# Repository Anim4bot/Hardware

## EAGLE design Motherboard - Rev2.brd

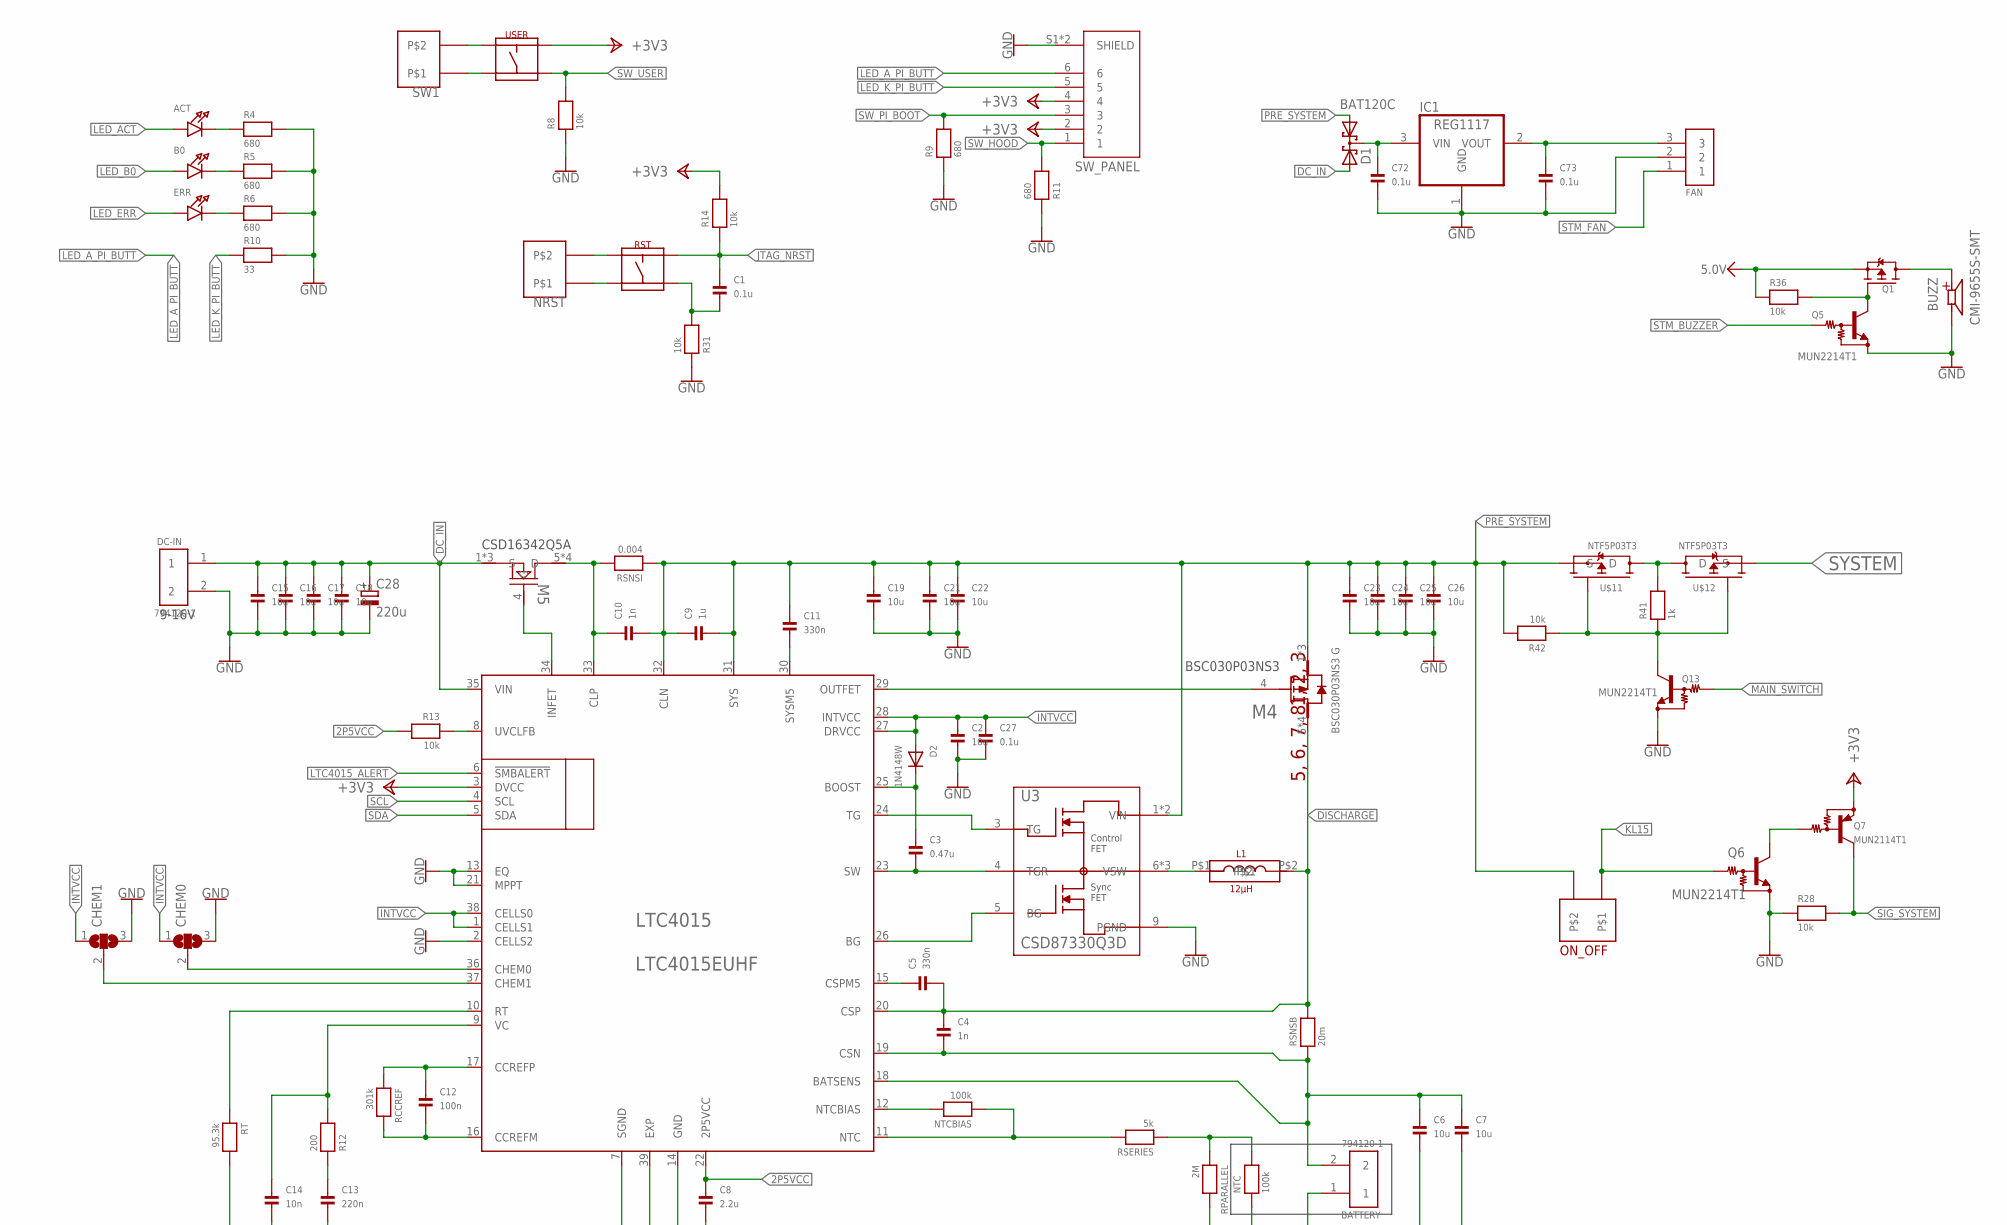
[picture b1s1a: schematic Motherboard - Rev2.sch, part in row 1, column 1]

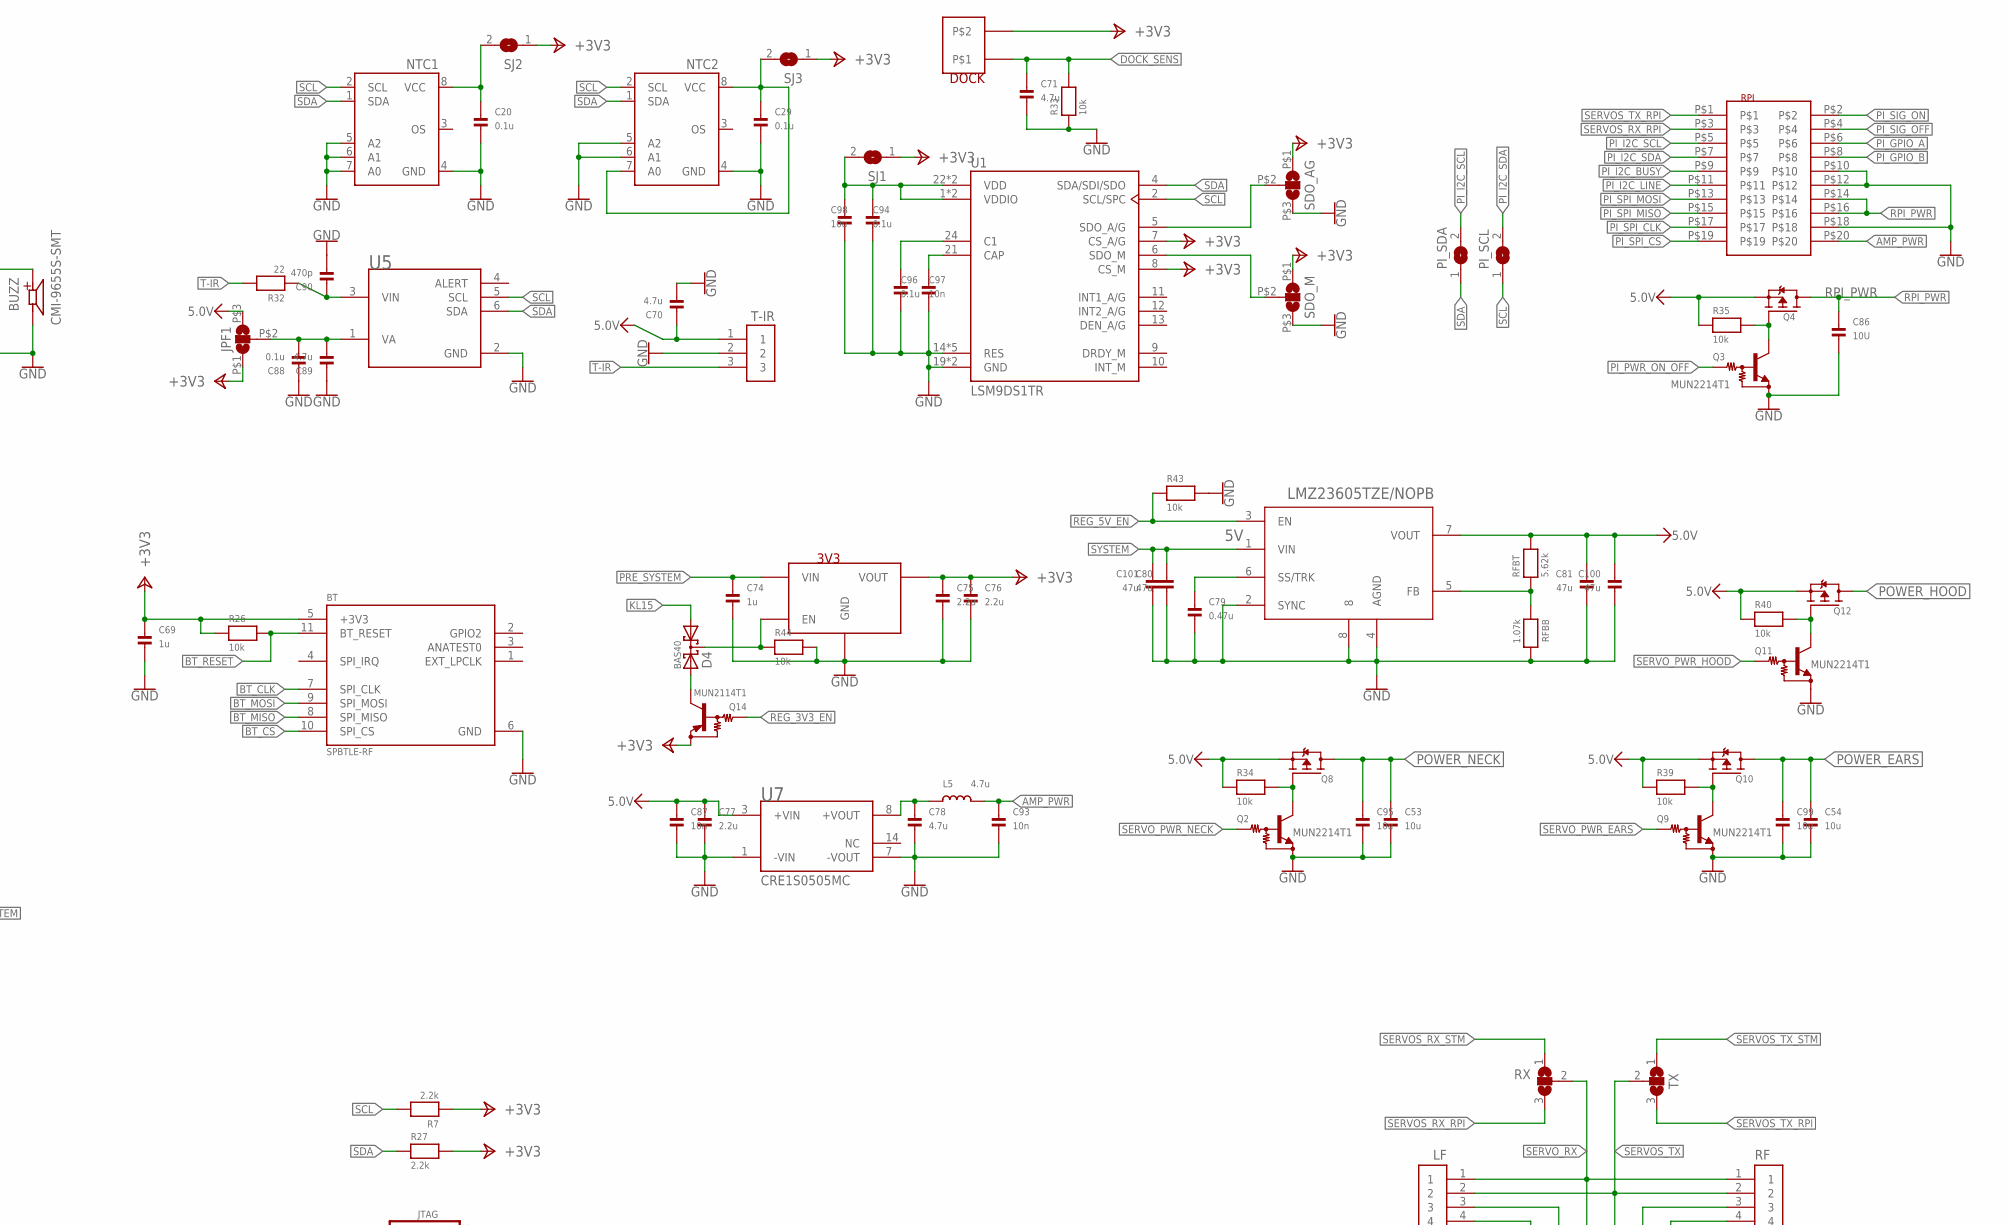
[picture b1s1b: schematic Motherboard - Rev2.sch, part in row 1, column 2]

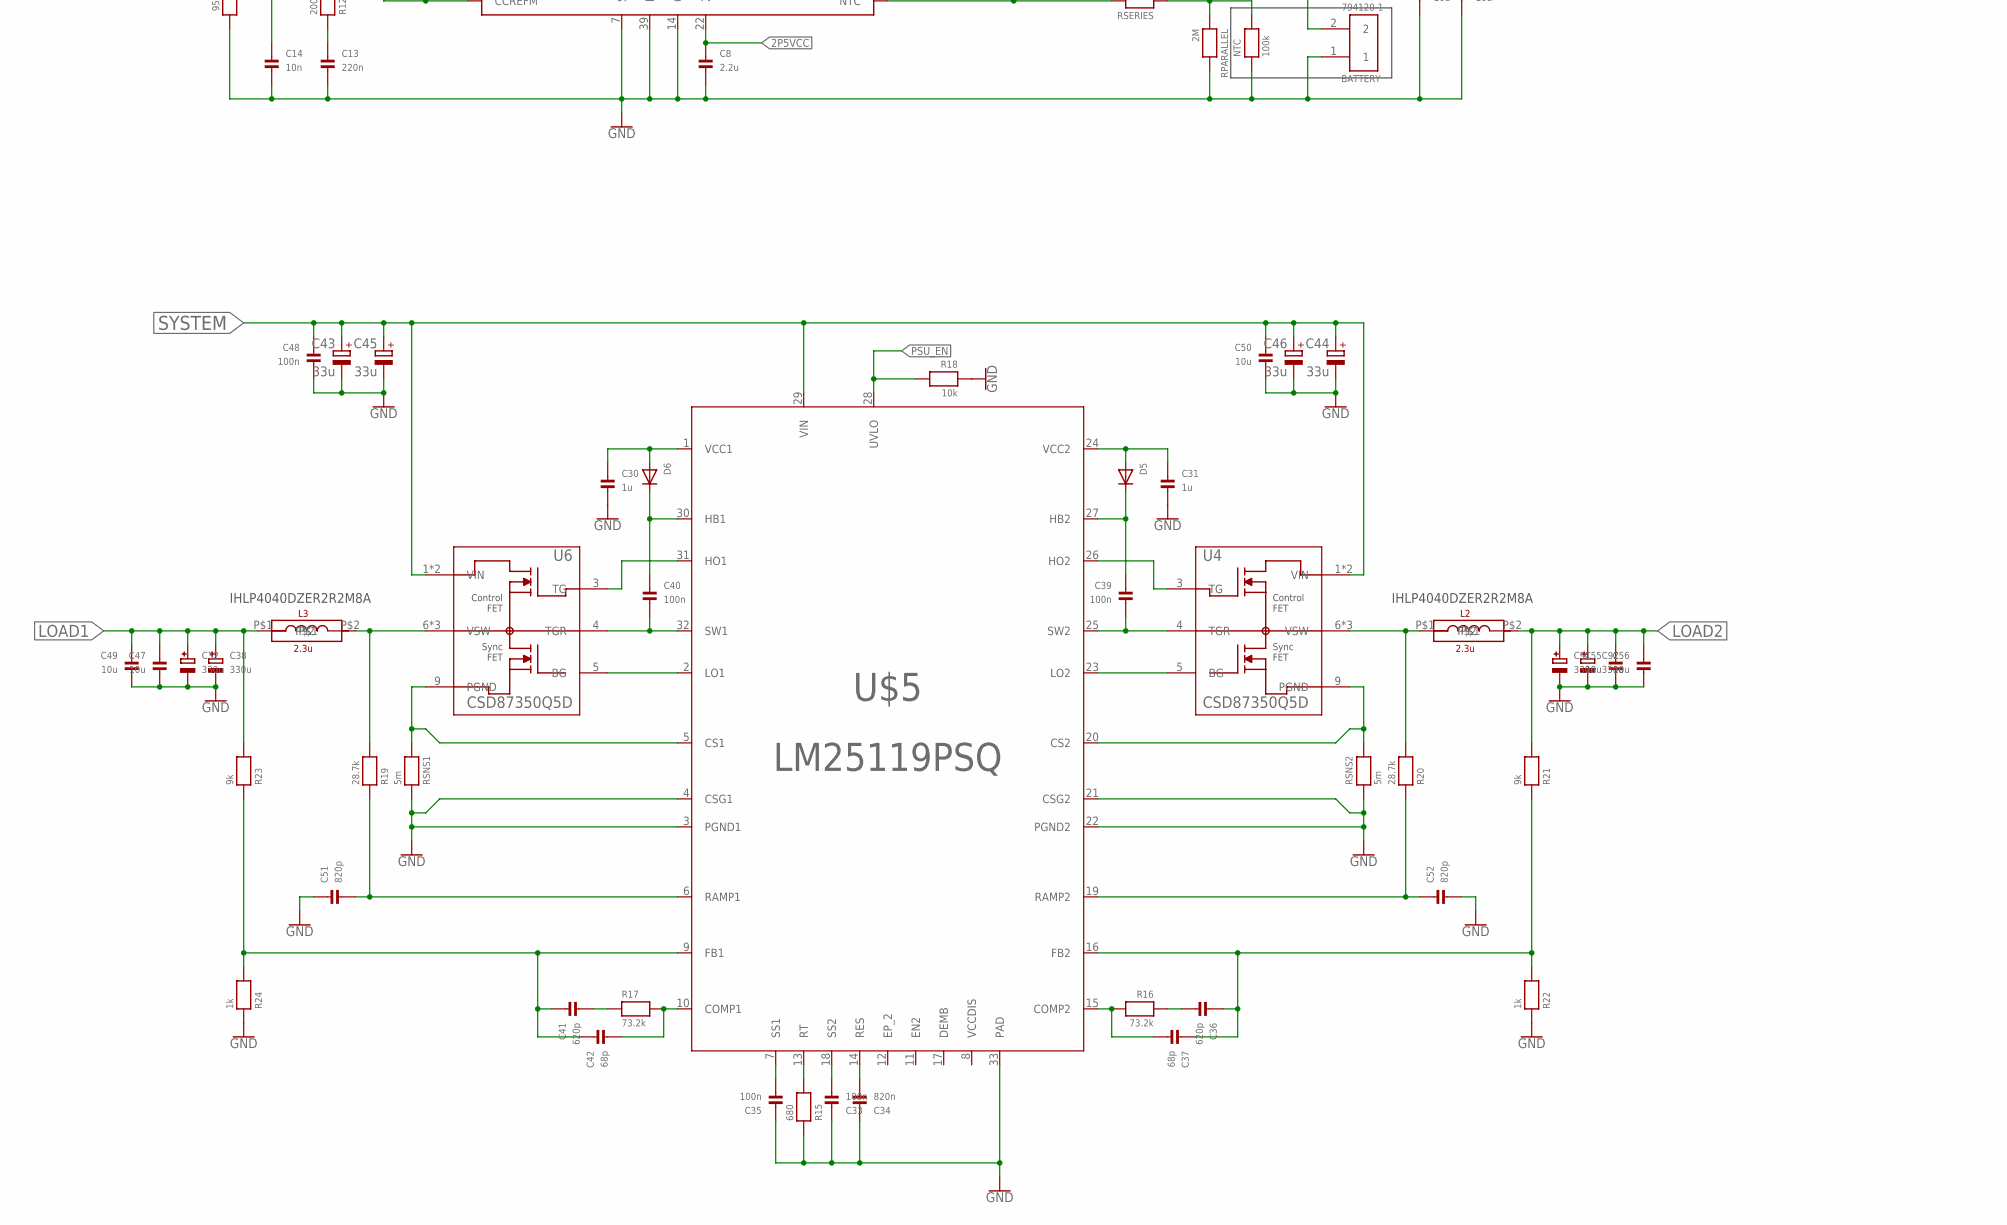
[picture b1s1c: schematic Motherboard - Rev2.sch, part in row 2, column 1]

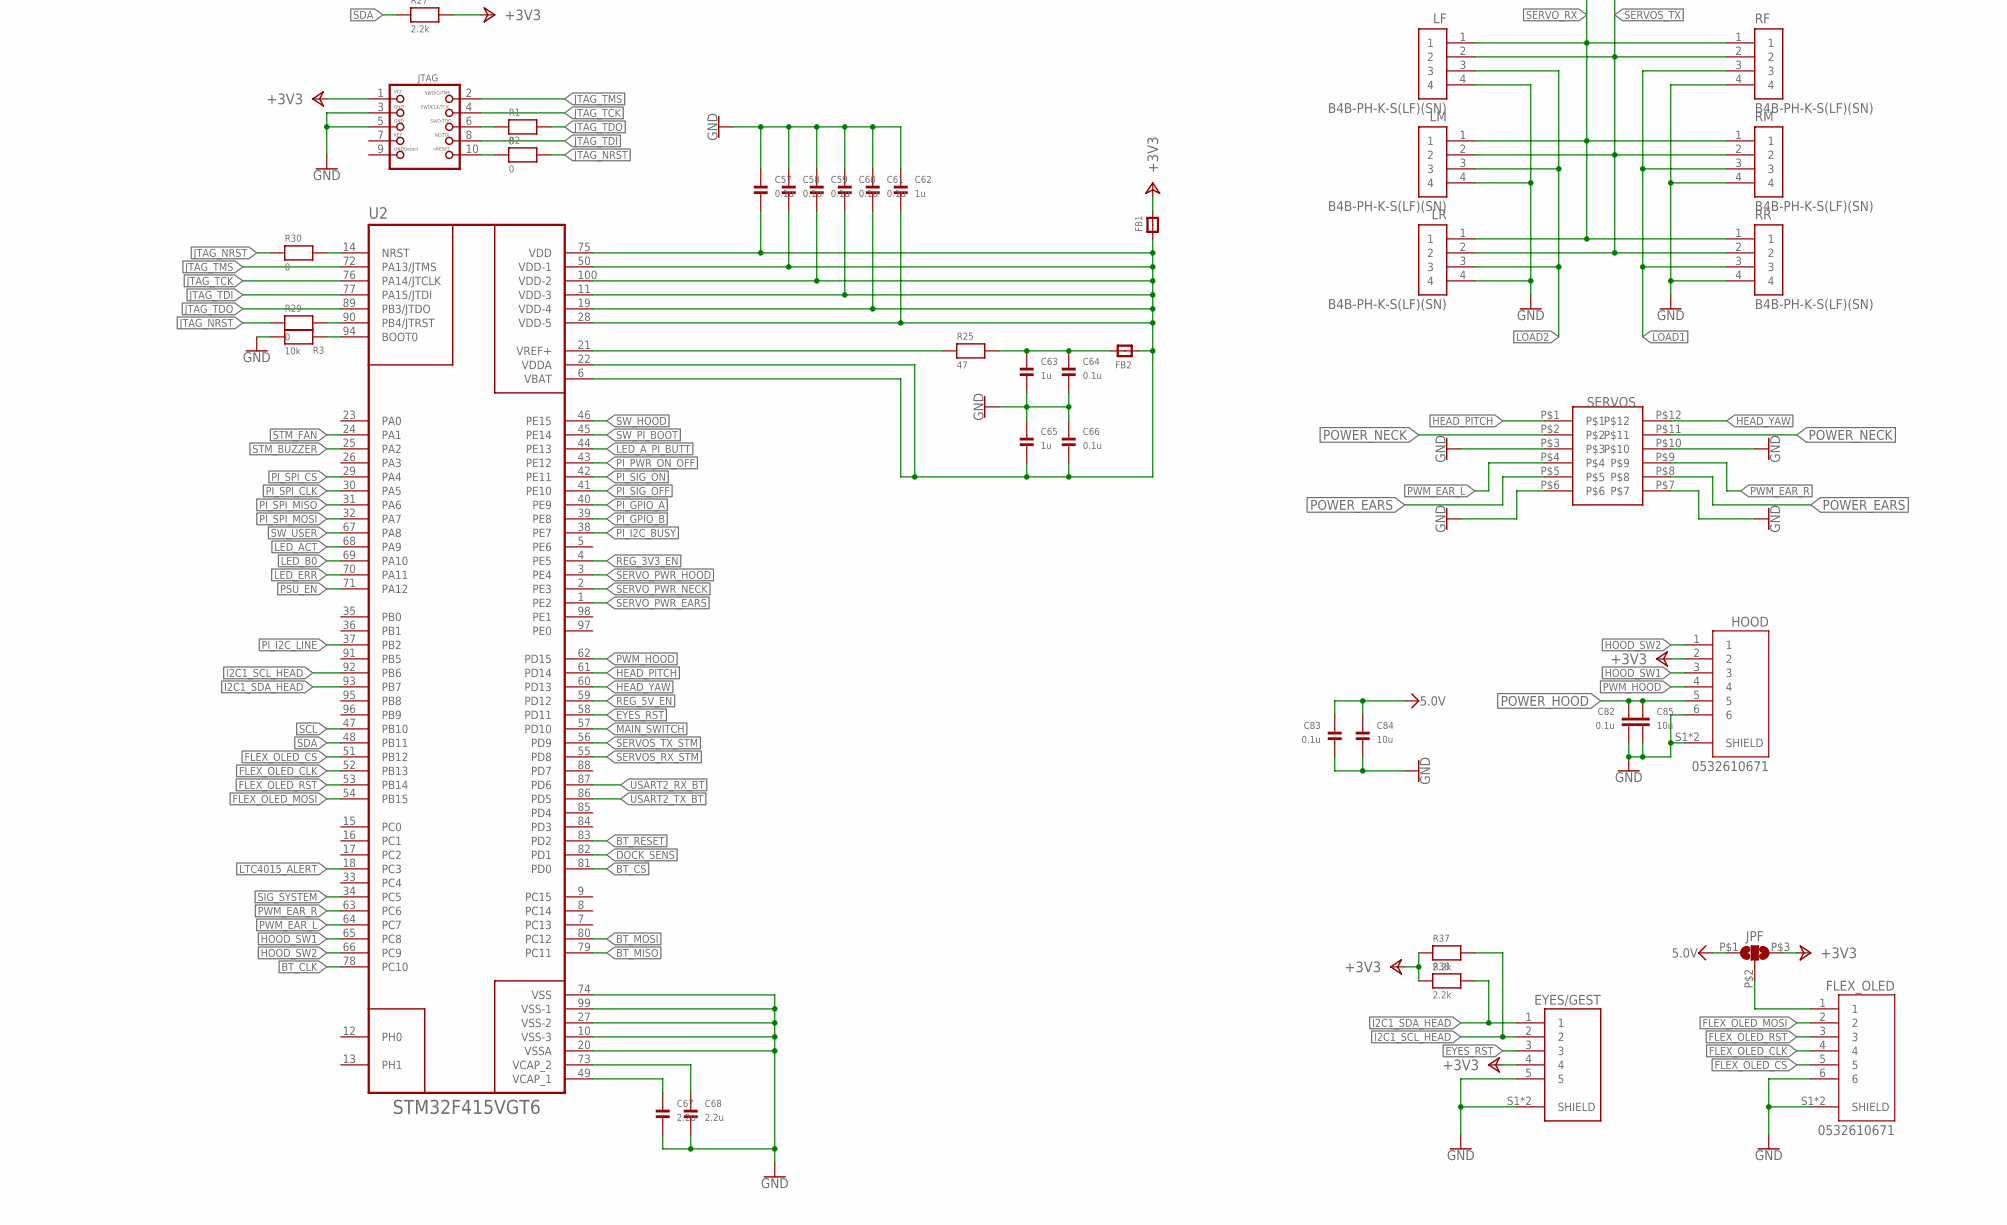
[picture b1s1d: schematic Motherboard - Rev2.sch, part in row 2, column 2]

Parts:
3V3: NCP5500DT-33.50-RKG
5V: LMZ23605TZE/NOPB; TZA07A
ACT: LED0805; CHIPLED_0805
B0: LED0805; CHIPLED_0805
BATTERY: 794120-1; TE_794120-1
BT: SPBTLE-RF; XCVR_SPBTLE-RF
BUZZ: CMI-9655S-SMT; CUI_CMI-9655S-SMT
C1, C20, C27, C29, C57, C58, C59, C60, C61, C64, C66, C72, C73, C82, C83, C88, C94, C96: 0.1u; 0805
C2, C98: 10u; 0805
C3, C79: 0.47u; 0805
C4, C10: 1n; 0805
C5, C11: 330n; 0805
C6, C7, C15, C16, C17, C18, C19, C21, C22, C23, C24, C25, C26, C47, C49, C50, C53, C54, C55, C56, C84, C85, C95, C99: 10u; 1206
C8, C67, C68, C75, C76, C77: 2.2u; 0805
C9, C30, C31, C62, C63, C65, C69, C74: 1u; 0805
C12, C33, C35, C39, C40: 100n; 0805
C13: 220n; 0805
C14, C87, C93, C97: 10n; 0805
C28: 220u; UD-10X10_NICHICON
C32, C38, C91, C92: 330u; EIA7343-31/D-R
C34: 820n; 0805
C36, C41: 620p; 0805
C37, C42: 68p; 0805
C43, C44, C45, C46: 33u; UD-6,3X7,7_NICHICON
C48: 100n; 1206
C51, C52: 820p; 0805
C70, C71, C78, C89: 4.7u; 0805
C80, C81, C100, C101: 47u; 1206
C86: 10U; 0805
C90: 470p; 0805
CHEM0, CHEM1: SJ2W; SJ_2
D1: BAT120C; SOT223
D2: 1N4148W; SOD-123
D4: BAS40; SOT23
D5, D6: DIODESOD-123; SOD-123
DC-IN: 794120-1; TE_794120-1
DOCK: MOLEX_53398
ERR: LED0805; CHIPLED_0805
EYES/GEST: 0532610571; MOLEX_0532610571
FAN: 0532610371; MOLEX_0532610371
FB1, FB2: FERRITE_0805; _0805
FLEX_OLED: 0532610671; MOLEX_0532610671
HOOD: 0532610671; MOLEX_0532610671
IC1: REG1117; SOT223
JPF, JPF1: SJ2WSJ_3; SJ_3
JTAG: JTAG-CORTEXM3; 2X05_1.27MM_SMT
L1: 12µH; SRR1210-680MTR
L2, L3: 2.3u; SRR1210-680MTR
L5: 4.7u; 0805
LF: B4B-PH-K-S(LF)(SN); JST_B4B-PH-K-S(LF)(SN)
LM: B4B-PH-K-S(LF)(SN); JST_B4B-PH-K-S(LF)(SN)
LR: B4B-PH-K-S(LF)(SN); JST_B4B-PH-K-S(LF)(SN)
LTC4015: LTC4015EUHF; QFN50P700X500X80-39N
M4: INFINEON_BSC030P03NS3_GINFINEON_BSC030P03NS3_G_0_0; INFINEON_BSC030P03NS3_G_0
M5: CSD16342Q5A-REV2; DQJ8
NRST: MOLEX_53398
NTC: 100k; 1206
NTC1, NTC2: TEMP_LM75B; TSSOP8
NTCBIAS: 100k; 0805
ON_OFF: MOLEX_53398
PI_SCL: SOLDERJUMPERREFLOW; SOLDERJUMPER_REFLOW
PI_SDA: SOLDERJUMPERREFLOW; SOLDERJUMPER_REFLOW
Q1, Q4, Q8, Q10, Q12: MOSFET-PWIDE; SOT23-WIDE
Q2, Q3, Q5, Q6, Q9, Q11, Q13: MUN2214T1; SC59-BEC
Q7, Q14: MUN2114T1; SC59-BEC
R1, R2, R29, R30: 0; 0805
R3, R8, R13, R14, R18, R26, R28, R31, R33, R34, R35, R36, R39, R40, R42, R43, R44: 10k; 0805
R4, R5, R6, R9, R11, R15: 680; 0805
R7, R27, R37, R38: 2.2k; 0805
R10: 33; 0805
R12: 200; 0805
R16, R17: 73.2k; 0805
R19, R20: 28.7k; 0805
R21, R23: 9k; 0805
R22, R24, R41: 1k; 0805
R25: 47; 0805
R32: 22; 0805
RCCREF: 301k; 0805
RF: B4B-PH-K-S(LF)(SN); JST_B4B-PH-K-S(LF)(SN)
RFBB: 1.07k; 0805
RFBT: 5.62k; 0805
RM: B4B-PH-K-S(LF)(SN); JST_B4B-PH-K-S(LF)(SN)
RPARALLEL: 2M; 0805
RPI: DF50-20DP-1V
RR: B4B-PH-K-S(LF)(SN); JST_B4B-PH-K-S(LF)(SN)
RSERIES: 5k; 0805
RSNS1, RSNS2: 5m; 2012
RSNSB: 20m; 2012
RSNSI: 0.004; 2012
RST: MJTP1140ATR
RT: 95.3k; 0805
RX: SJ2W; SJ_2
SDO_AG: SJ2WSJ_3; SJ_3
SDO_M: SJ2WSJ_3; SJ_3
SERVOS: BM12B-ZPDSS-TF
SJ1, SJ2, SJ3: SOLDERJUMPER; SOLDERJUMPER_ARROW_NOPASTE
SW1: MOLEX_53398
SW_PANEL: 0532610671; MOLEX_0532610671
T-IR: 0532610371; MOLEX_0532610371
TX: SJ2W; SJ_2
U1: LSM9DS1TR; PQFN43P300X350X102-24N
U2: STM32F415VGT6; QFP50P1600X1600X160-100N
U3: CSD87330Q3D; DQZ8_1P8X2P7
U4, U6: CSD87350Q5D; DQY8_3P2X4P3
U5: TEXAS_INSTRUMENTS_ADC101C021CIMK-NOPBTEXAS_INSTRU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; TEXAS_INSTRUMENTS_ADC101C021CIMK-NOPB_0
U7: CRE1S0505MC; SOIC254P1110X700-5N
U$5: LM25119PSQ; SQA32A
U$11, U$12: NTF5P03T3; SOT223
USER: MJTP1140ATR

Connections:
2P5VCC: C8.1, LTC4015.22 (2P5VCC), R13.2
5.0V: 5V.7 (VOUT), C70.1, C77.1, C81.1, C83.1, C84.1, C87.1, C100.1, JPF.P$1 (1), JPF1.P$3 (3), Q1.2 (S), Q4.2 (S), Q8.2 (S), Q10.2 (S), Q12.2 (S), R34.1, R35.1, R36.1, R39.1, R40.1, RFBT.2, T-IR.1, U7.3 (+VIN)
5V_FAN: C73.1, FAN.3, IC1.2 (VOUT)
+3V3: 3V3.VOUT, BT.5 (+3V3), C69.1, C75.1, C76.1, DOCK.P$2, EYES/GEST.4, FB1.2, HOOD.2, JPF.P$3 (3), JPF1.P$1 (1), JTAG.1, LTC4015.3 (DVCC), Q7.E, Q14.E, R7.1, R14.2, R26.1, R27.2, R37.1, R38.1, SDO_AG.P$1 (1), SDO_M.P$1 (1), SJ1.1, SJ2.1, SJ3.1, SW_PANEL.2, SW_PANEL.4, U1.7 (CS_A/G), U1.8 (CS_M), USER.P$2
AMP_PWR: C93.1, L5.2, RPI.P$20
BATT: BATTERY.2, C4.2, C6.1, C7.1, LTC4015.18 (BATSENS), LTC4015.19 (CSN), RSNSB.1
BG: LTC4015.26 (BG), U3.5 (BG)
BT_CLK: BT.7 (SPI_CLK), U2.78 (PC10)
BT_CS: BT.10 (SPI_CS), U2.81 (PD0)
BT_MISO: BT.8 (SPI_MISO), U2.79 (PC11)
BT_MOSI: BT.9 (SPI_MOSI), U2.80 (PC12)
BT_RESET: BT.11 (BT_RESET), R26.2, U2.83 (PD2)
CCREFM: C12.2, LTC4015.16 (CCREFM), RCCREF.2
CCREFP: C12.1, LTC4015.17 (CCREFP), RCCREF.1
CHEM0: CHEM0.2, LTC4015.36 (CHEM0)
CHEM1: CHEM1.2, LTC4015.37 (CHEM1)
CLP: C10.1, LTC4015.33 (CLP), M5.5 (D), M5.6 (D), M5.7 (D), M5.8 (D), RSNSI.2
COMP1: C42.2, R17.2, U$5.10 (COMP1)
COMP2: C37.2, R16.2, U$5.15 (COMP2)
CS1: RSNS1.2, U6.9 (PGND), U$5.5 (CS1)
CS2: RSNS2.2, U4.9 (PGND), U$5.20 (CS2)
DC_IN: C15.1, C16.1, C17.1, C18.1, C28.+, D1.3 (A2), DC-IN.1, LTC4015.35 (VIN), M5.1 (S), M5.2 (S), M5.3 (S)
DISCHARGE: C4.1, C5.2, L1.P$2, LTC4015.20 (CSP), M4.5 (2_DRAIN), M4.6 (2_DRAIN), M4.7 (2_DRAIN), M4.8 (2_DRAIN), RSNSB.2
DOCK_SENS: C71.1, DOCK.P$1, R33.2, U2.82 (PD1)
EYES_RST: EYES/GEST.3, U2.58 (PD11)
FB1: C41.1, C42.1, R23.1, R24.2, U$5.9 (FB1)
FB2: C36.1, C37.1, R21.1, R22.2, U$5.16 (FB2)
FLEX_OLED_CLK: FLEX_OLED.4, U2.52 (PB13)
FLEX_OLED_CS: FLEX_OLED.5, U2.51 (PB12)
FLEX_OLED_MOSI: FLEX_OLED.2, U2.54 (PB15)
FLEX_OLED_RST: FLEX_OLED.3, U2.53 (PB14)
GND: 3V3.GND, 5V.2 (SYNC), 5V.4 (AGND), 5V.8, BATTERY.1, BT.6 (GND), BUZZ.N, C2.2, C6.2, C7.2, C8.2, C13.2, C14.2, C15.2, C16.2, C17.2, C18.2, C19.2, C20.2, C21.2, C22.2, C23.2, C24.2, C25.2, C26.2, C27.2, C28.-, C29.2, C30.2, C31.2, C32.-, C33.1, C34.1, C35.1, C38.-, C43.-, C44.-, C45.-, C46.-, C47.2, C48.2, C49.2, C50.2, C51.1, C52.2, C53.2, C54.2, C55.2, C56.2, C57.1, C58.1, C59.1, C60.1, C61.1, C62.1, C63.2, C64.2, C65.1, C66.1, C67.2, C68.2, C69.2, C70.2, C71.2, C72.2, C73.2, C74.2, C75.2, C76.2, C77.2, C78.2, C79.2, C80.2, C81.2, C82.2, C83.2, C84.2, C85.2, C86.2, C87.2, C88.1, C89.1, C90.2, C91.-, C92.-, C93.2, C94.2, C95.2, C96.2, C97.2, C98.2, C99.2, C100.2, C101.2, CHEM0.3, CHEM1.3, DC-IN.2, EYES/GEST.5, EYES/GEST.S1 (SHIELD), EYES/GEST.S2 (SHIELD), FAN.2, FLEX_OLED.6, FLEX_OLED.S1 (SHIELD), FLEX_OLED.S2 (SHIELD), HOOD.6, HOOD.S1 (SHIELD), HOOD.S2 (SHIELD), IC1.1 (GND), JTAG.3, JTAG.5, LF.4, LM.4, LR.4, LTC4015.2 (CELLS2), LTC4015.7 (SGND), LTC4015.13 (EQ), LTC4015.14 (GND), LTC4015.21 (MPPT), LTC4015.39 (EXP), NTC.1, NTC1.4 (GND), NTC1.5 (A2), NTC1.6 (A1), NTC1.7 (A0), NTC2.4 (GND), NTC2.5 (A2), NTC2.6 (A1), Q2.E, Q3.E, Q5.E, Q6.E, Q9.E, Q11.E, Q13.E, R3.1, R4.2, R5.2, R6.2, R8.1, R9.1, R10.2, R11.1, R15.1, R18.1, R22.1, R24.1, R28.1, R31.1, R33.1, R43.2, R44.2, RF.4, RFBB.2, RM.4, RPARALLEL.2, RPI.P$10, RPI.P$12, RPI.P$18, RR.4, RSNS1.1, RSNS2.1, RT.2, SDO_AG.P$3 (3), SDO_M.P$3 (3), SERVOS.P$3, SERVOS.P$6, SERVOS.P$7, SERVOS.P$10, SW_PANEL.S1 (SHIELD), SW_PANEL.S2 (SHIELD), T-IR.2, U1.14 (RES), U1.15 (RES), U1.16 (RES), U1.17 (RES), U1.18 (RES), U1.19 (GND), U1.20 (GND), U2.10 (VSS-3), U2.20 (VSSA), U2.27 (VSS-2), U2.74 (VSS), U2.99 (VSS-1), U3.9 (PGND), U5.2 (GND), U7.1 (-VIN), U7.7 (-VOUT), U$5.3 (PGND1), U$5.4 (CSG1), U$5.21 (CSG2), U$5.22 (PGND2), U$5.33 (PAD)
HEAD_PITCH: SERVOS.P$1, U2.61 (PD14)
HEAD_YAW: SERVOS.P$12, U2.60 (PD13)
HO1: U6.3 (TG), U$5.31 (HO1)
HO2: U4.3 (TG), U$5.26 (HO2)
HOOD_SW1: HOOD.3, U2.65 (PC8)
HOOD_SW2: HOOD.1, U2.66 (PC9)
I2C1_SCL_HEAD: EYES/GEST.2, R37.2, U2.92 (PB6)
I2C1_SDA_HEAD: EYES/GEST.1, R38.2, U2.93 (PB7)
INFET: LTC4015.34 (INFET), M5.4 (G)
INTVCC: C2.1, C27.1, CHEM0.1, CHEM1.1, D2.A, LTC4015.1 (CELLS1), LTC4015.27 (DRVCC), LTC4015.28 (INTVCC), LTC4015.38 (CELLS0)
JTAG_NRST: C1.1, R2.2, R14.1, R29.1, R30.1, RST.P$2
JTAG_TCK: JTAG.4, U2.76 (PA14/JTCLK)
JTAG_TDI: JTAG.8, U2.77 (PA15/JTDI)
JTAG_TDO: R1.2, U2.89 (PB3/JTDO)
JTAG_TMS: JTAG.2, U2.72 (PA13/JTMS)
KL15: D4.1 (A1), ON_OFF.P$1, Q6.B
LED_ACT: ACT.A, U2.68 (PA9)
LED_A_PI_BUTT: SW_PANEL.6, U2.44 (PE13)
LED_B0: B0.A, U2.69 (PA10)
LED_ERR: ERR.A, U2.70 (PA11)
LED_K_PI_BUTT: R10.1, SW_PANEL.5
LO1: U6.5 (BG), U$5.2 (LO1)
LO2: U4.5 (BG), U$5.23 (LO2)
LOAD1: C32.+, C38.+, C47.1, C49.1, L3.P$1, R23.2, RF.3, RM.3, RR.3
LOAD2: C55.1, C56.1, C91.+, C92.+, L2.P$2, LF.3, LM.3, LR.3, R21.2
LTC4015_ALERT: LTC4015.6 (!SMBALERT), U2.18 (PC3)
MAIN_SWITCH: Q13.B, U2.57 (PD10)
unnamed: C90.1, R32.1, U5.3 (VIN)
unnamed: NRST.P$1, RST.P$4
unnamed: Q2.C, Q8.1 (G), R34.2
unnamed: Q3.C, Q4.1 (G), R35.2
unnamed: ERR.C, R6.1
unnamed: B0.C, R5.1
unnamed: JTAG.6, R1.1
unnamed: JTAG.10, R2.1
unnamed: ACT.C, R4.1
unnamed: C72.1, D1.4 (K1K2), IC1.3 (VIN)
unnamed: NRST.P$2, RST.P$1
unnamed: Q9.C, Q10.1 (G), R39.2
unnamed: C78.1, L5.1, U7.8 (+VOUT)
unnamed: LTC4015.12 (NTCBIAS), NTCBIAS.2
unnamed: Q11.C, Q12.1 (G), R40.2
unnamed: C3.1, D2.C, LTC4015.25 (BOOST)
unnamed: R29.2, U2.90 (PB4/JTRST)
unnamed: R3.2, U2.94 (BOOT0)
unnamed: R41.2, U$11.4 (D), U$12.4 (D)
unnamed: C5.1, LTC4015.15 (CSPM5)
unnamed: Q13.C, R41.1, R42.1, U$11.1 (G), U$12.1 (G)
unnamed: Q1.1 (G), Q5.C, R36.2
unnamed: Q6.C, Q7.B
unnamed: R30.2, U2.14 (NRST)
unnamed: SW1.P$1, USER.P$4
unnamed: 3V3.EN, D4.3 (C), R44.1
unnamed: C13.1, R12.1
unnamed: D4.2 (A2), Q14.C
unnamed: C1.2, R31.2, RST.P$3
unnamed: C68.1, U2.73 (VCAP_2)
unnamed: LTC4015.8 (UVCLFB), R13.1
unnamed: R15.2, U$5.13 (RT)
unnamed: C67.1, U2.49 (VCAP_1)
unnamed: BUZZ.P, Q1.3 (D)
unnamed: R25.1, U2.21 (VREF+)
unnamed: C36.2, R16.1
unnamed: C57.2, C58.2, C59.2, C60.2, C61.2, C62.2, C65.2, C66.2, FB1.1, FB2.1, U2.6 (VBAT), U2.11 (VDD-3), U2.19 (VDD-4), U2.22 (VDDA), U2.28 (VDD-5), U2.50 (VDD-1), U2.75 (VDD), U2.100 (VDD-2)
unnamed: C63.1, C64.1, FB2.2, R25.2
unnamed: C39.1, D5.C, U$5.27 (HB2)
unnamed: NTC.2, RPARALLEL.1, RSERIES.1
unnamed: C96.1, U1.24 (C1)
unnamed: C97.1, U1.21 (CAP)
unnamed: SDO_M.P$2 (2), U1.6 (SDO_M)
unnamed: SDO_AG.P$2 (2), U1.5 (SDO_A/G)
unnamed: FLEX_OLED.1, JPF.P$2 (2)
unnamed: C88.2, C89.2, JPF1.P$2 (2), U5.1 (VA)
unnamed: SW1.P$2, USER.P$1
unnamed: C40.1, D6.C, U$5.30 (HB1)
unnamed: 5V.5 (FB), RFBB.1, RFBT.1
unnamed: C20.1, NTC1.8 (VCC), SJ2.2
unnamed: C41.2, R17.1
unnamed: C94.1, C98.1, SJ1.2, U1.1 (VDDIO), U1.3 (VDDIO), U1.22 (VDD), U1.23 (VDD)
unnamed: 5V.6 (SS/TRK), C79.1
unnamed: C29.1, NTC2.7 (A0), NTC2.8 (VCC), SJ3.2
unnamed: L3.P$2, R19.2, U6.6 (VSW), U6.7 (VSW), U6.8 (VSW)
unnamed: L2.P$1, R20.2, U4.6 (VSW), U4.7 (VSW), U4.8 (VSW)
NTC: LTC4015.11 (NTC), NTCBIAS.1, RSERIES.2
OUTFET: LTC4015.29 (OUTFET), M4.4 (GATE)
PI_GPIO_A: RPI.P$6, U2.40 (PE9)
PI_GPIO_B: RPI.P$8, U2.39 (PE8)
PI_I2C_BUSY: RPI.P$9, U2.38 (PE7)
PI_I2C_LINE: RPI.P$11, U2.37 (PB2)
PI_I2C_SCL: PI_SDA.2, RPI.P$5
PI_I2C_SDA: PI_SCL.2, RPI.P$7
PI_PWR_ON_OFF: Q3.B, U2.43 (PE12)
PI_SIG_OFF: RPI.P$4, U2.41 (PE10)
PI_SIG_ON: RPI.P$2, U2.42 (PE11)
PI_SPI_CLK: RPI.P$17, U2.30 (PA5)
PI_SPI_CS: RPI.P$19, U2.29 (PA4)
PI_SPI_MISO: RPI.P$15, U2.31 (PA6)
PI_SPI_MOSI: RPI.P$13, U2.32 (PA7)
POWER_EARS: C54.1, C99.1, Q10.3 (D), SERVOS.P$5, SERVOS.P$8
POWER_HOOD: C82.1, C85.1, HOOD.5, Q12.3 (D)
POWER_NECK: C53.1, C95.1, Q8.3 (D), SERVOS.P$2, SERVOS.P$11
PRE_SYSTEM: 3V3.VIN, C9.1, C9.2, C10.2, C11.1, C19.1, C21.1, C22.1, C23.1, C24.1, C25.1, C26.1, C74.1, D1.1 (A1), LTC4015.31 (SYS), LTC4015.32 (CLN), M4.1 (2_SOURCE), M4.2 (2_SOURCE), M4.3 (2_SOURCE), ON_OFF.P$2, R42.2, RSNSI.1, U3.1 (VIN), U3.2 (VIN), U$11.3 (S)
PSU_EN: R18.2, U2.71 (PA12), U$5.28 (UVLO)
PWM_EAR_L: SERVOS.P$4, U2.64 (PC7)
PWM_EAR_R: SERVOS.P$9, U2.63 (PC6)
PWM_HOOD: HOOD.4, U2.62 (PD15)
RAMP1: C51.2, R19.1, U$5.6 (RAMP1)
RAMP2: C52.1, R20.1, U$5.19 (RAMP2)
REG_3V3_EN: Q14.B, U2.4 (PE5)
REG_5V_EN: 5V.3 (EN), R43.1, U2.59 (PD12)
RES: C34.2, U$5.14 (RES)
RPI_PWR: C86.1, Q4.3 (D), RPI.P$14, RPI.P$16
RT: LTC4015.10 (RT), RT.1
SCL: LTC4015.4 (SCL), NTC1.2 (SCL), NTC2.2 (SCL), PI_SCL.1, R7.2, U1.2 (SCL/SPC), U2.47 (PB10), U5.5 (SCL)
SDA: LTC4015.5 (SDA), NTC1.1 (SDA), NTC2.1 (SDA), PI_SDA.1, R27.1, U1.4 (SDA/SDI/SDO), U2.48 (PB11), U5.6 (SDA)
SERVOS_RX_RPI: RPI.P$3, RX.3
SERVOS_RX_STM: RX.1, U2.55 (PD8)
SERVOS_TX: LF.2, LM.2, LR.2, RF.2, RM.2, RR.2, TX.2
SERVOS_TX_RPI: RPI.P$1, TX.3
SERVOS_TX_STM: TX.1, U2.56 (PD9)
SERVO_PWR_EARS: Q9.B, U2.1 (PE2)
SERVO_PWR_HOOD: Q11.B, U2.3 (PE4)
SERVO_PWR_NECK: Q2.B, U2.2 (PE3)
SERVO_RX: LF.1, LM.1, LR.1, RF.1, RM.1, RR.1, RX.2
SIG_SYSTEM: Q7.C, R28.2, U2.34 (PC5)
SS1: C35.2, U$5.7 (SS1)
SS2: C33.2, U$5.18 (SS2)
STM_BUZZER: Q5.B, U2.25 (PA2)
STM_FAN: FAN.1, U2.24 (PA1)
SW1: C40.2, U6.4 (TGR), U$5.32 (SW1)
SW2: C39.2, U4.4 (TGR), U$5.25 (SW2)
SW_HOOD: R11.2, SW_PANEL.1, U2.46 (PE15)
SW_PI_BOOT: R9.2, SW_PANEL.3, U2.45 (PE14)
SW_USER: R8.2, U2.67 (PA8), USER.P$3
SYSMS: C11.2, LTC4015.30 (SYSM5)
SYSTEM: 5V.1 (VIN), C43.+, C44.+, C45.+, C46.+, C48.1, C50.1, C80.1, C101.1, U4.1 (VIN), U4.2 (VIN), U6.1 (VIN), U6.2 (VIN), U$5.29 (VIN), U$12.3 (S)
T-IR: R32.2, T-IR.3
TG: LTC4015.24 (TG), U3.3 (TG)
TGR: C3.2, LTC4015.23 (SW), U3.4 (TGR)
USART2_RX_BT: U2.87 (PD6)
USART2_TX_BT: U2.86 (PD5)
VC: C14.1, LTC4015.9 (VC), R12.2
VCC1: C30.1, D6.A, U$5.1 (VCC1)
VCC2: C31.1, D5.A, U$5.24 (VCC2)
VSW: L1.P$1, U3.6 (VSW), U3.7 (VSW), U3.8 (VSW)

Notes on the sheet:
CSD16342Q5A
BSC030P03NS3
9-16V
IHLP4040DZER2R2M8A

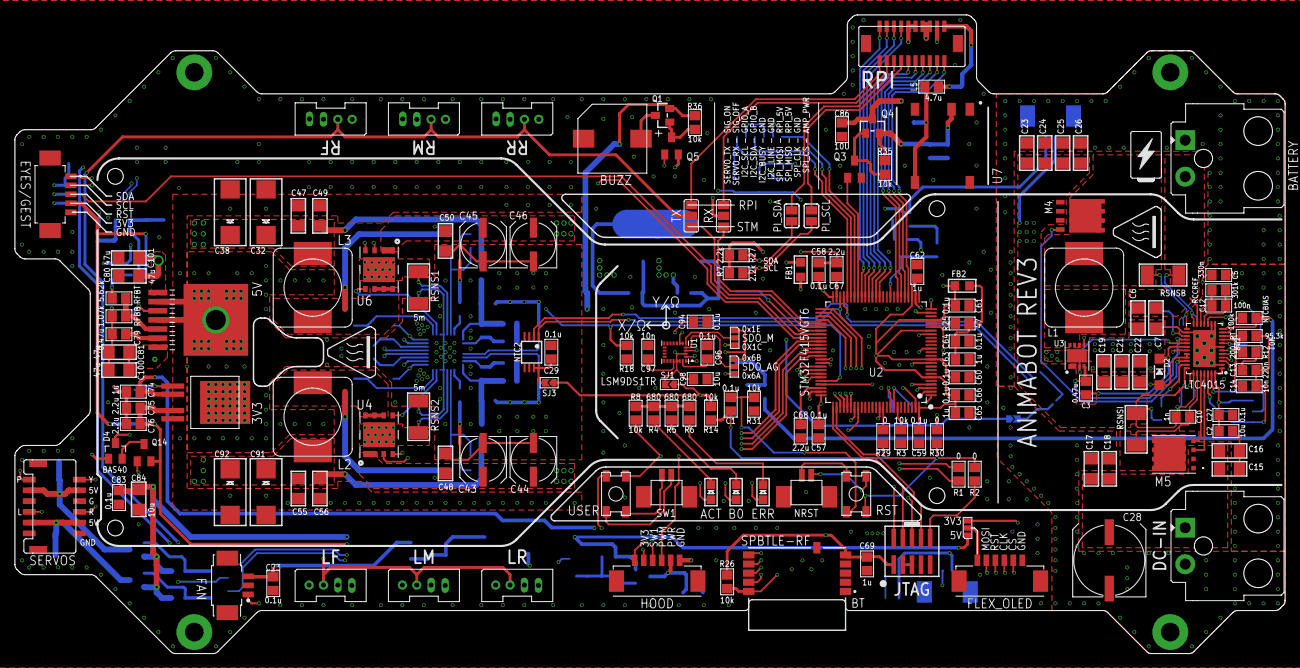
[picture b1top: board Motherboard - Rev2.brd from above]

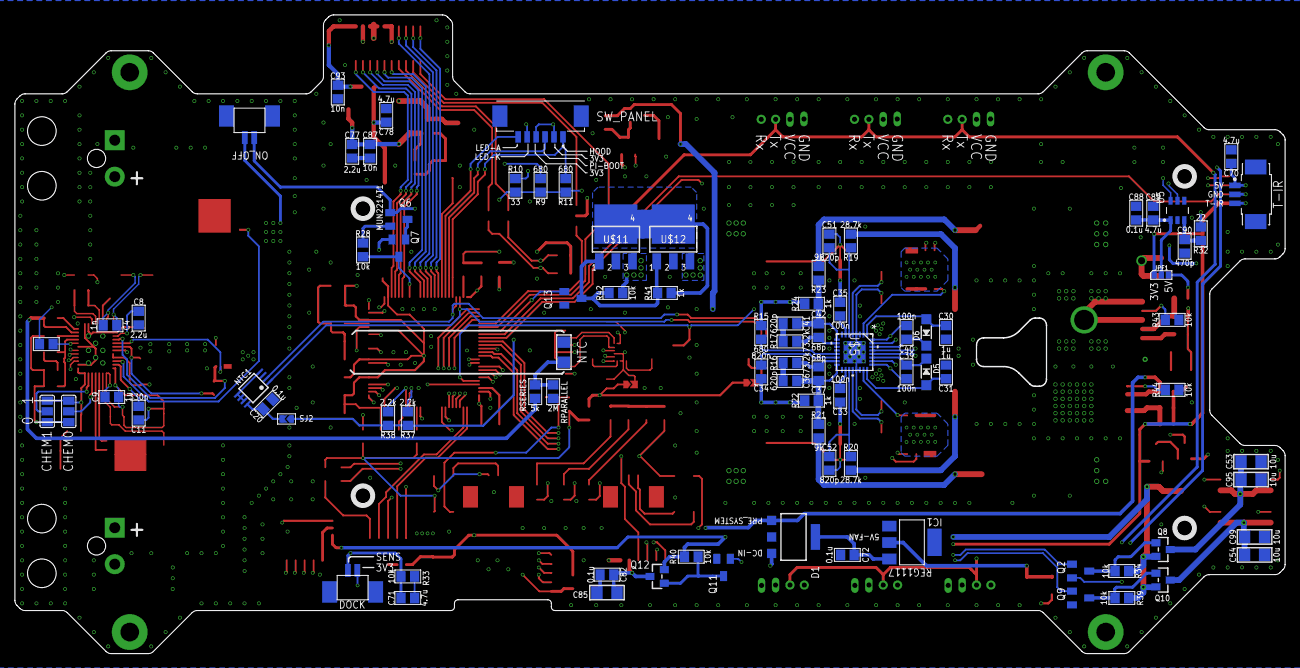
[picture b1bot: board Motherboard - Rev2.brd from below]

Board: 4 copper layers, 177.0 x 89.0 mm, 241 parts (88 on the bottom side), 175 nets.

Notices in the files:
Motherboard - Rev2.sch:
Animabot's Hardware design - Property of Emmanuel Sichet - Attribution-NonCommercial-NoDerivatives 4.0 International (CC BY-NC-ND 4.0)
parts and their libraries:
microbuilder: This work is placed in the public domain, and may be freely used for commercial and non-commercial work with the following conditions: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
SparkFun-PowerSymbols: Licensing: Creative Commons ShareAlike 4.0 International - https://creativecommons.org/licenses/by-sa/4.0
